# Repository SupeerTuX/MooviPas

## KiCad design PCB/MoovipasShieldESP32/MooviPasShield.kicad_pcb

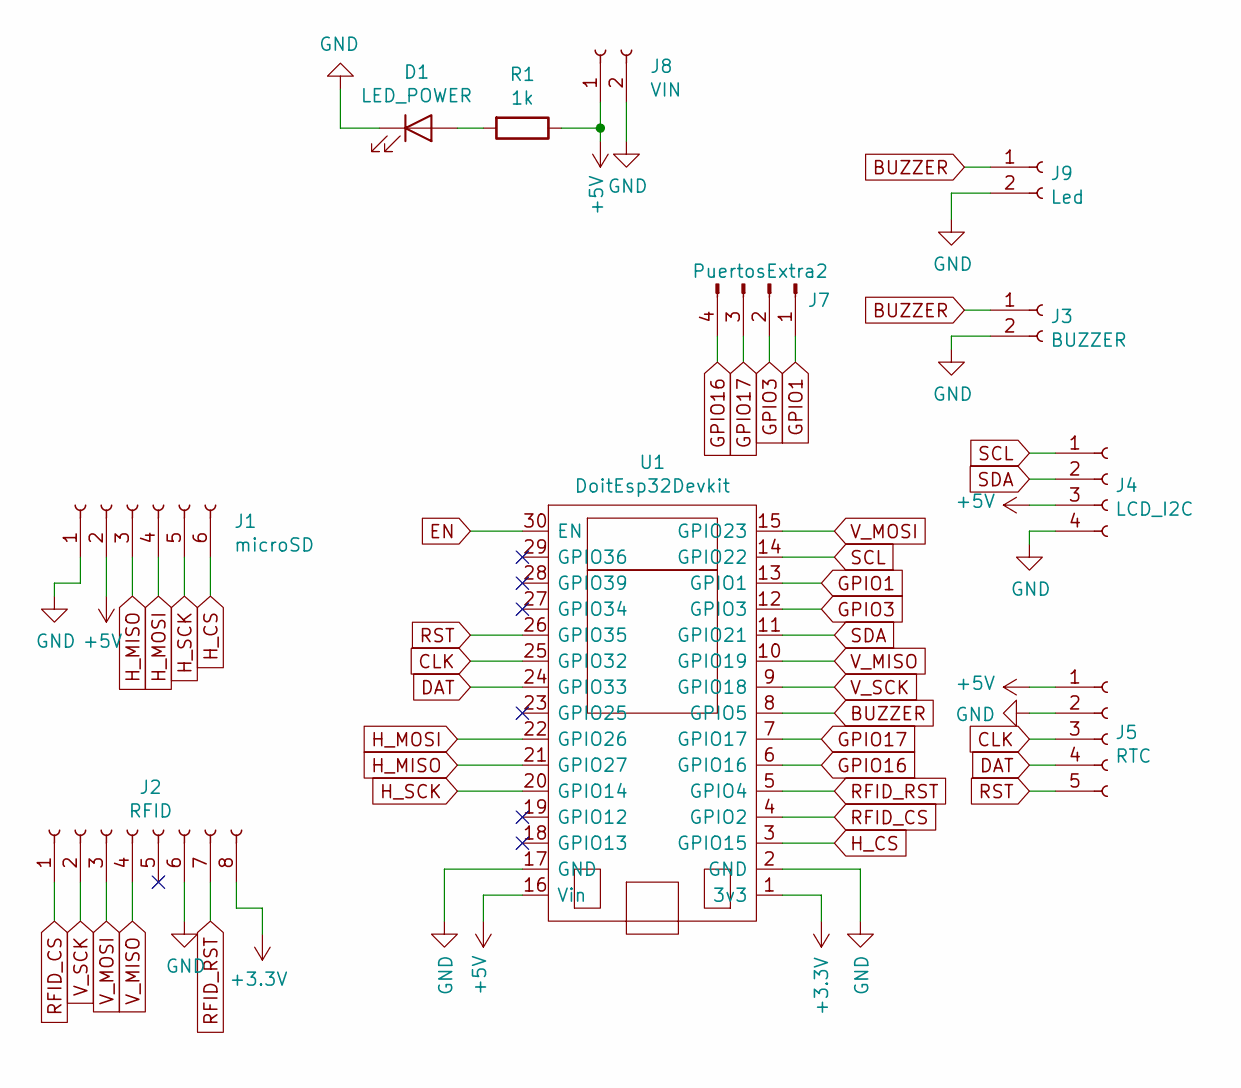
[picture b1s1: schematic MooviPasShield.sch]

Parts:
D1: LED_POWER; LED_D5.0mm
J1: microSD; Socket_Strip_Angled_1x06_Pitch2.54mm
J2: RFID; Pin_Header_Straight_1x08_Pitch2.54mm
J3: BUZZER; Socket_Strip_Straight_1x02_Pitch2.54mm
J4: LCD_I2C; Pin_Header_Straight_1x04_Pitch2.54mm
J5: RTC; Pin_Header_Straight_1x05_Pitch2.54mm
J7: PuertosExtra2; Socket_Strip_Straight_1x04_Pitch2.54mm
J8: VIN; Socket_Strip_Straight_1x02_Pitch2.54mm
J9: Led; TerminalBlock_bornier-2_P5.08mm
R1: 1k; R_Axial_DIN0204_L3.6mm_D1.6mm_P7.62mm_Horizontal
U1: DoitEsp32Devkit; DoitESP32

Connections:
+3V3: J2.8, U1.1 (3v3)
+5V: J1.2, J4.3, J5.1, J8.1, R1.1, U1.16 (Vin)
BUZZER: J3.1, J9.1, U1.8 (GPIO5)
CLK: J5.3, U1.25 (GPIO32)
DAT: J5.4, U1.24 (GPIO33)
EN: U1.30 (EN)
GND: D1.1 (K), J1.1, J2.6, J3.2, J4.4, J5.2, J8.2, J9.2, U1.2 (GND), U1.17 (GND)
GPIO1: J7.1, U1.13 (GPIO1)
GPIO3: J7.2, U1.12 (GPIO3)
GPIO16: J7.4, U1.6 (GPIO16)
GPIO17: J7.3, U1.7 (GPIO17)
H_CS: J1.6, U1.3 (GPIO15)
H_MISO: J1.3, U1.21 (GPIO27)
H_MOSI: J1.4, U1.22 (GPIO26)
H_SCK: J1.5, U1.20 (GPIO14)
unnamed: D1.2 (A), R1.2
RFID_CS: J2.1, U1.4 (GPIO2)
RFID_RST: J2.7, U1.5 (GPIO4)
RST: J5.5, U1.26 (GPIO35)
SCL: J4.1, U1.14 (GPIO22)
SDA: J4.2, U1.11 (GPIO21)
V_MISO: J2.4, U1.10 (GPIO19)
V_MOSI: J2.3, U1.15 (GPIO23)
V_SCK: J2.2, U1.9 (GPIO18)

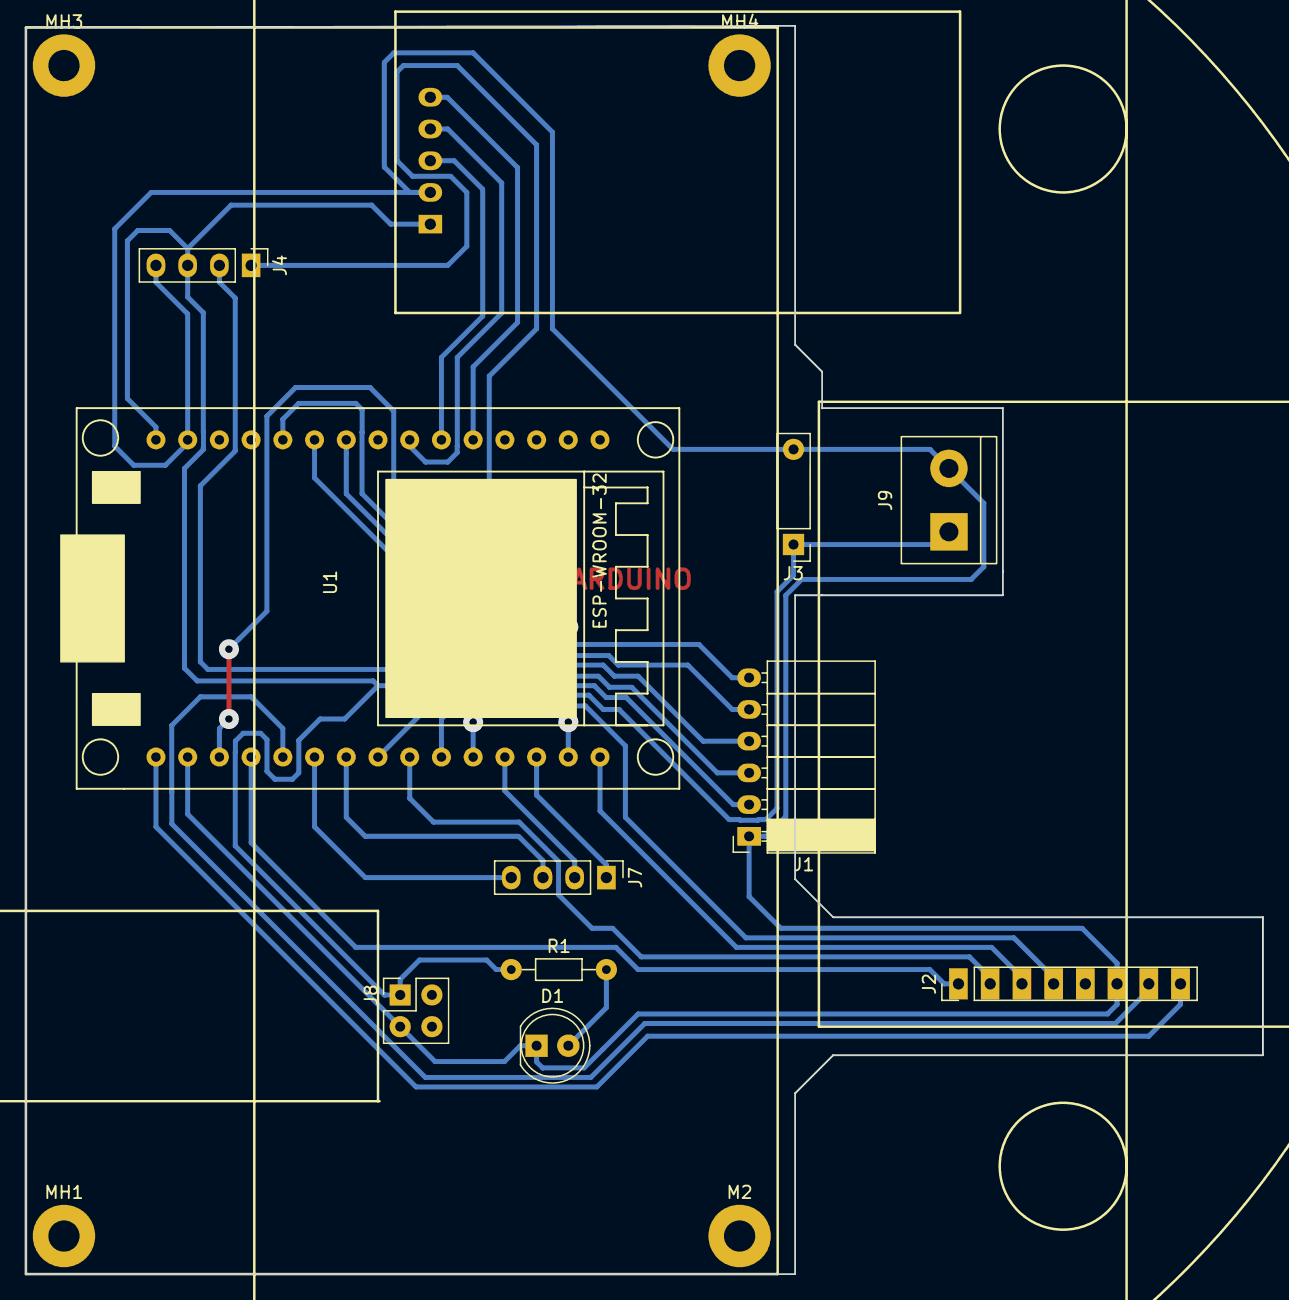
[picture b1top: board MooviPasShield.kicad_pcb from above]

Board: 2 copper layers, 99.1 x 99.9 mm, 15 parts (1 on the bottom side), 23 nets.

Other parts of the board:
M2: MH2; MountingHole_2.5mm_Pad
MH1: MH1; MountingHole_2.5mm_Pad
MH3: MH3; MountingHole_2.5mm_Pad
MH4: MH4; MountingHole_2.5mm_Pad

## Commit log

2019-04-02 Version inicial
2019-04-03 Wifi y MFRC522 funcionando
2019-04-03 Test de commit
2019-04-05 EEprom incluida
2019-04-05 RTC DS1302 agregado
2019-04-06 Interfaz microSD agregada
2019-04-08 Cambio de puerto RTC y SD
2019-04-11 PCB Terminado 1 cara con 4 puentes
2019-04-12 PCB actualizado
2019-04-12 BackUp pcb borrado
2019-04-12 Funciones de lcdi2c separadas de main
2019-04-15 Footprint esp32 modificado
2019-04-16 Verion de fabricacion
2019-04-16 Cambio de .ini monitor_speed
2019-04-17 RTC y LCD separados
2019-04-21 Guarda de texto agregada
2019-04-21 Archivo con funciones Wifi separados
2019-04-24 Version funcional backup en ls SD
